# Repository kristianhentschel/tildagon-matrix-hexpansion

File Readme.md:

# Matrix Hexpansion

This repository contains the firmware and hardware projects for the **Matrix Hexpansion** and the CH32V006 breakout hexpansion it is based on. This is an add-on for the EMF Camp Tildagon/Spaceagon [badge](https://tildagon.badge.emfcamp.org/).

The hexpansion can be controlled with the [Matrix Hexpansion companion app](https://github.com/kristianhentschel/tildagon-matrix-hexpansion-app). The processor refreshes the LED Matrix using DMA (up to 156 LEDs with charlieplexing on its 13 available GPIO pins) and can run animated patterns or scrolling text configured by the badge over the I2C interface.

Assembled hexpansions will be available to buy from [shop.alwaysplottingsomething.com](https://shop.alwaysplottingsomething.com/category/hexpansions).

Note that the LEDs are only a single colour, and not as bright as the WS2812B/NeoPixel-style RGB LEDs seen on other hexpansions. On the other hand, you can have multiple of these plugged in without running down your battery in minutes!

## Base CH32V006 prototyping hexpansion

The common base board with the hexpansion connector must be produced with ENIG finish and holds the processor, status LEDs, configuration jumpers, and I2C pull-up resistors. It has large through hole pads for all GPIO pins and Hexpansion connector pins for a daughter board to connect to. There are also debug pads for I2C, power, and a USB programmer like the WCH LinkE.

I use the CH32V006F8U6/7 processor and program it with the [ch32fun framework](https://github.com/cnlohr/ch32fun). The CH32V003F4U6 has the same pinout and footprint, but may not have enough flash and RAM to run the matrix, control interface, and animation. If you get an assembled board from me, the processor is already programmed with a bootloader so firmware programs can be flashed from the badge without buying the dedicated USB debugger.

There is no dedicated EEPROM on the board, but the microcontroller is connected to the I2C bus and can emulate a read-only EEPROM interface if desired.

## Daughter board

Daughter boards are soldered to the base's pads, usually with SMD pads on the bottom. They can be cheaper to manufacture at low quantities (e.g. use HASL finish). The `lite-loop` board used in the Matrix Hexpansion is an example.

## Hardware

The `boards` directory contains KiCad projects and schematics for the PCBs.

* `base_v2_lite`: The base hexpansion board; with a CH32V006 co-processor and all GPIO pins and hexpansion interface pins broken out to through-hole pads.
* `lite_loop`: The 156-LED matrix display daughter board (13 pin charlie-plexing, arranged in 8 rows of 18 columns and a 9th row of 12 columns). Six instances of this make a circle surrounding the badge.

There is also a symbol library and footprints to aid in making custom daughter boards.

## Firmware

The RISC-V CH32V006 processor on the base board runs native firmware code built with the [ch32fun framework](https://github.com/cnlohr/ch32fun).

* `firmware/lite_loop` is the driver for the `lite-loop` daughter board. It maintains the LED matrix display, can run animations and scrolling text patterns, and presents an I2C interface for identifying and controlling the hexpansion from the badge.
* `firmware/bootloader_006` presents an I2C EEPROM-like interface if the `PD7` pin is pulled low during boot, so the badge can write the (non-bootloader) code flash area to replace the main program with a new firmware image.
* `firmware/blink` is a very small hello-world program that just toggles the PA1 pin attached to the status LED. It is useful when bulk provisioning or as a starting point for using the base without the lite-loop daughter board.

### Developing custom firmware

You can use the badge app to upload your own firmware program to the microcontroller on the hexpansion, for example to write your own animated patterns. To get set up you will need a few things:

1. A RISC-V toolchain, see instructions at https://github.com/cnlohr/ch32fun/wiki/Installation (building their `minichlink` and getting a USB debugger is optional as we will be using the badge to upload our firmware image).
2. A way to upload files to the badge over the USB connection, such as [mpremote](https://docs.micropython.org/en/latest/reference/mpremote.html) or [Thonny](https://thonny.org/).
3. The ["Matrix Hexpansion" app](https://apps.badge.emfcamp.org/apps/41214133), from the Tildagon app store.

Then follow these steps to upload firmware using the badge app:

1. Compile the firmware image
2. Copy the firmware image `.bin` file to the "Matrix Hexpansion" app's `assets/` folder
3. Reboop the badge
4. Open the app, and select "Firmware Upgrade", the target hexpansion slot, and your custom image.

```sh
# get the ch32fun repository
git submodule update --init --recursive

# make a copy of the lite-loop firmware to start from
cd firmware
cp -r lite_loop my_firmware

# build your firmware binary
cd my_firmware
make build

# copy the firmware image to the badge file system
mpremote cp main.bin :/apps/kristianhentschel_tildagon_matrix_hexpansion_app/assets/my_firmware.bin
```

To get started, place this code at the top of the `loop()` function in `my_firmware/main.c`:

```c
// void loop() {
  while(true) {
    for (int frame = 0; frame < 2 * LEDS_GRID_COLS; frame++) {
      for (int row = 0; row < LEDS_GRID_ROWS; row++) {
        for (int col = 0; col < LEDS_GRID_COLS; col++) {
          // Find the frame buffer index of the LED at the current row and column:
          int index = leds_grid_indices[row * LEDS_GRID_COLS + col];
          // In the array of grid indices some values are 255, because the first row only has 12 LEDs instead of 18, so skip those:
          if (index >= LEDS_COUNT) continue;
          
          // Set the LED to on or off depending on the current frame
          if (frame < LEDS_GRID_COLS) {
            frame_buffer[index] = col < frame ? 255 : 0;
          } else {
            frame_buffer[index] = col >= frame - LEDS_GRID_COLS ? 255 : 0;
          }
        }
      }

      Delay_Ms(40);
    }
  }

  // ... existing loop code, unreachable
// }
```

You may also wish to change the name in the hexpansion header; this will stop the app attempting to control it. Replace the `friendly_name` value in the hexpansion header (it must still be at most 9 characters; fill any extra slots with `0`):

```c
// static hexpansion_header_t g_hexpansion_header = {
  // ...
  // .friendly_name = {'L', 'i', 't', 'e', 'l', 'o', 'o', 'p', 0},
  .friendly_name = {'M', 'y', ' ', 'M', 'a', 't', 'r', 'i', 'x'},
// };
```

You can use the defined LED positions in [leds.h]() (using the `leds_polar_positions` and `leds_grid_indices` variables); or you could add to the list of animations, keep the name, and modify the badge app to trigger them.

Note this is all still somewhat of a prototype, for example I may change the position values to an integer representation, or come up with a system for the app to discover custom patterns to make this easier in future versions. It would also be nice to synchronise animations across multiple hexpansions.

### Bootloader and provisioning

To provision a factory-fresh processor, the bootloader must first be flashed and configured using a dedicated programmer like the WCH-LinkE and the ch32fun `minichlink` tool. We must flash the flash bootloader, configure PD7 use as GPIO rather than reset, and flash a main program. I use the `blink` program during provisioning because it is quick to build and upload; the lite_loop program is then flashed from the badge during testing. The `provision.sh` script does these steps, optionally in a loop:

```sh
./provision.sh --app blink --bootloader --loop
```
For end users, firmware updates can be applied from the badge app and a dedicated programmer is not required (but may still be helpful for debugging if writing your own firmware).

## Note on previous iteration

The base is called `v2` because the first iteration of this also had a [IS31FL3731](https://lumissil.com/assets/pdf/core/IS31FL3731_DS.pdf) LED driver, but this was found to add unnecessary cost and complexity and was never assembled or programmed properly. I suspect it would be able to drive the LED's quite a bit more brightly and consistently! In the current `v2` the current limiting resistors were moved to the daughter board and the breakout pads have a more useful generic layout, also including the hexpansion connector pins.

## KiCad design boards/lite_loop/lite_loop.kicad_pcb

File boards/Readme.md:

# Boards

* `base_v2_lite` is the base board. It has to be manufactured as a 1mm board with ENIG.
* `lite_loop` is the main "Matrix Hexpansion" LED daughter board. It can be connected to the top of the base board with solder paste and a hot air tool.

# Symbols and Footprints

* `matrix-hexpansion.kicad_sym` has schematic symbols for the base board's breakout pin array, including a version that only has the first two rows of pins as used on the `lite_loop` board.
* `matrix-hexpansion.pretty` is a footprint library including THT (used on the base) and SMD (used on the daughter boards) variations of the breakout pin array. The footprints have alignment aids on silkscreen and user layers.

# Acknowledgements

The base board is derived from the [badge-2024-hardware hexpansion template](https://github.com/emfcamp/badge-2024-hardware/tree/main/hexpansion) by kliment under CERN-OHL-P. The `hexpansion-edge-connector` symbol and footprint included with this repository for convenience are also from the same project.

# Stencils for previous version

If you want to make a stencil for your soldering kit picked up at EMF Camp 2026 (marked `v2`, `2026-05-22`), here are links to the [gerber files](https://stuff.5yk.de/20260719_lite_loop_gerber.zip) and [DXF exports](https://stuff.5yk.de/20260719_lite_loop_stencil.zip).

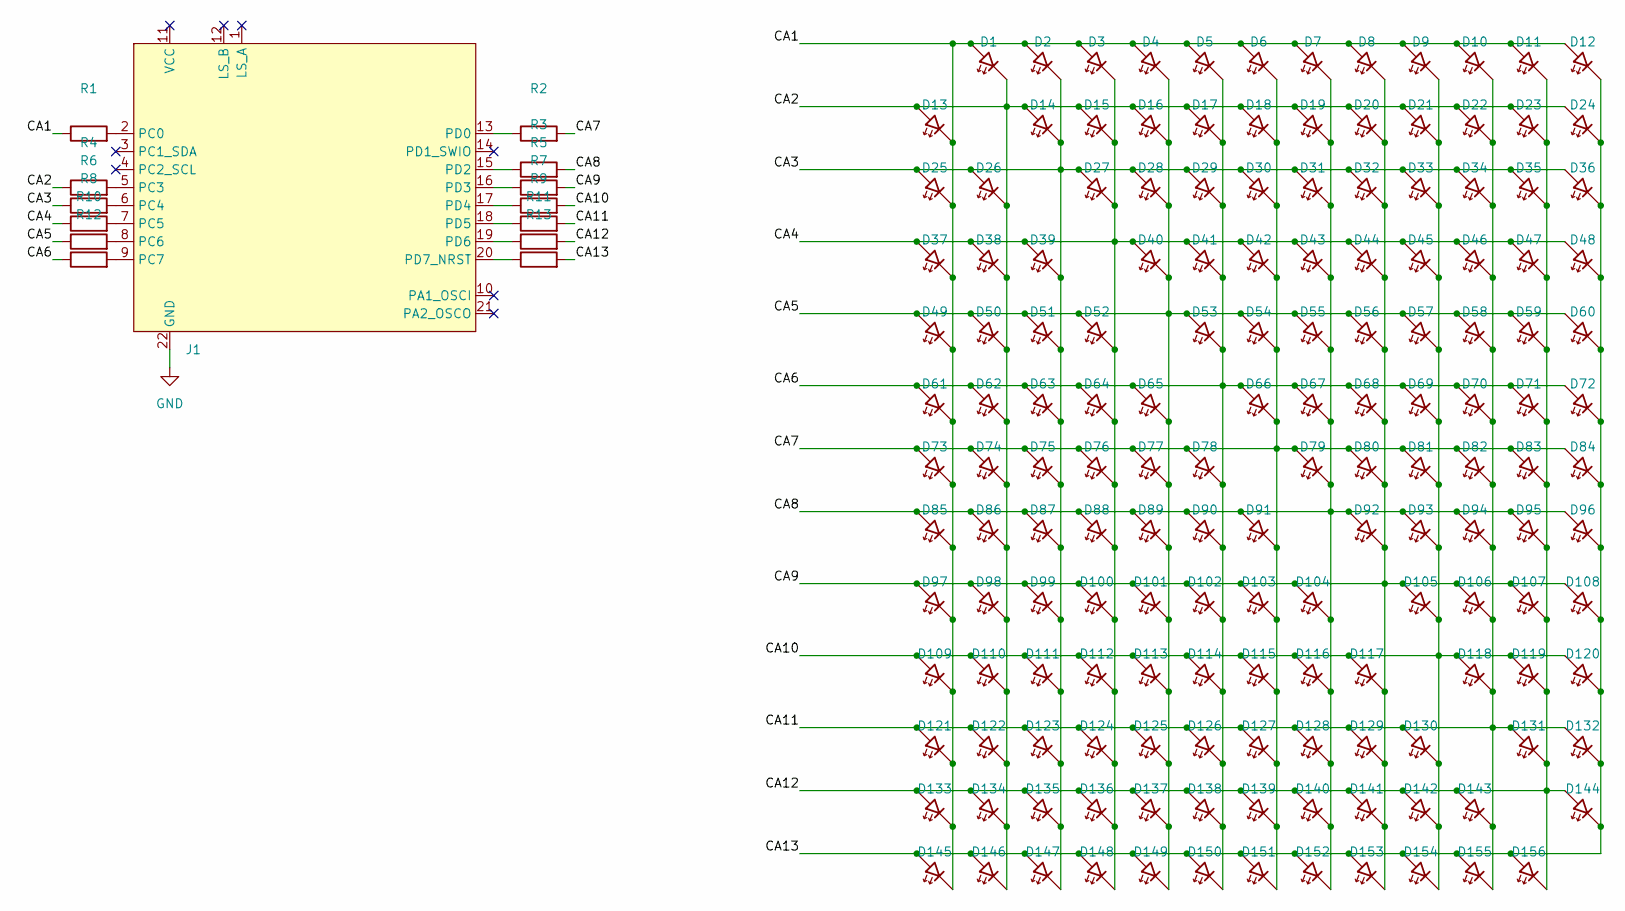
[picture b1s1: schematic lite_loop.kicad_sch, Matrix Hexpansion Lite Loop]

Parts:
D1, D2, D3, D4, D5, D6, D7, D8, D9, D10, D11, D12, D13, D14, D15, D16, D17, D18, D19, D20, D21, D22, D23, D24, D25, D26, D27, D28, D29, D30, D31, D32, D33, D34, D35, D36, D37, D38, D39, D40, D41, D42, D43, D44, D45, D46, D47, D48, D49, D50, D51, D52, D53, D54, D55, D56, D57, D58, D59, D60, D61, D62, D63, D64, D65, D66, D67, D68, D69, D70, D71, D72, D73, D74, D75, D76, D77, D78, D79, D80, D81, D82, D83, D84, D85, D86, D87, D88, D89, D90, D91, D92, D93, D94, D95, D96, D97, D98, D99, D100, D101, D102, D103, D104, D105, D106, D107, D108, D109, D110, D111, D112, D113, D114, D115, D116, D117, D118, D119, D120, D121, D122, D123, D124, D125, D126, D127, D128, D129, D130, D131, D132, D133, D134, D135, D136, D137, D138, D139, D140, D141, D142, D143, D144, D145, D146, D147, D148, D149, D150, D151, D152, D153, D154, D155, D156: LED; LED_0603_1608Metric
J1: matrix-hexpansion-base-v2-partial-SMD
R1, R2, R3, R4, R5, R6, R7, R8, R9, R10, R11, R12, R13: 100R; R_0603_1608Metric

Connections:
/CA1: D1.2 (A), D2.2 (A), D3.2 (A), D4.2 (A), D5.2 (A), D6.2 (A), D7.2 (A), D8.2 (A), D9.2 (A), D10.2 (A), D11.2 (A), D12.2 (A), D13.1 (K), D25.1 (K), D37.1 (K), D49.1 (K), D61.1 (K), D73.1 (K), D85.1 (K), D97.1 (K), D109.1 (K), D121.1 (K), D133.1 (K), D145.1 (K), R1.1
/CA2: D1.1 (K), D13.2 (A), D14.2 (A), D15.2 (A), D16.2 (A), D17.2 (A), D18.2 (A), D19.2 (A), D20.2 (A), D21.2 (A), D22.2 (A), D23.2 (A), D24.2 (A), D26.1 (K), D38.1 (K), D50.1 (K), D62.1 (K), D74.1 (K), D86.1 (K), D98.1 (K), D110.1 (K), D122.1 (K), D134.1 (K), D146.1 (K), R4.1
/CA3: D2.1 (K), D14.1 (K), D25.2 (A), D26.2 (A), D27.2 (A), D28.2 (A), D29.2 (A), D30.2 (A), D31.2 (A), D32.2 (A), D33.2 (A), D34.2 (A), D35.2 (A), D36.2 (A), D39.1 (K), D51.1 (K), D63.1 (K), D75.1 (K), D87.1 (K), D99.1 (K), D111.1 (K), D123.1 (K), D135.1 (K), D147.1 (K), R6.1
/CA4: D3.1 (K), D15.1 (K), D27.1 (K), D37.2 (A), D38.2 (A), D39.2 (A), D40.2 (A), D41.2 (A), D42.2 (A), D43.2 (A), D44.2 (A), D45.2 (A), D46.2 (A), D47.2 (A), D48.2 (A), D52.1 (K), D64.1 (K), D76.1 (K), D88.1 (K), D100.1 (K), D112.1 (K), D124.1 (K), D136.1 (K), D148.1 (K), R8.1
/CA5: D4.1 (K), D16.1 (K), D28.1 (K), D40.1 (K), D49.2 (A), D50.2 (A), D51.2 (A), D52.2 (A), D53.2 (A), D54.2 (A), D55.2 (A), D56.2 (A), D57.2 (A), D58.2 (A), D59.2 (A), D60.2 (A), D65.1 (K), D77.1 (K), D89.1 (K), D101.1 (K), D113.1 (K), D125.1 (K), D137.1 (K), D149.1 (K), R10.1
/CA6: D5.1 (K), D17.1 (K), D29.1 (K), D41.1 (K), D53.1 (K), D61.2 (A), D62.2 (A), D63.2 (A), D64.2 (A), D65.2 (A), D66.2 (A), D67.2 (A), D68.2 (A), D69.2 (A), D70.2 (A), D71.2 (A), D72.2 (A), D78.1 (K), D90.1 (K), D102.1 (K), D114.1 (K), D126.1 (K), D138.1 (K), D150.1 (K), R12.1
/CA7: D6.1 (K), D18.1 (K), D30.1 (K), D42.1 (K), D54.1 (K), D66.1 (K), D73.2 (A), D74.2 (A), D75.2 (A), D76.2 (A), D77.2 (A), D78.2 (A), D79.2 (A), D80.2 (A), D81.2 (A), D82.2 (A), D83.2 (A), D84.2 (A), D91.1 (K), D103.1 (K), D115.1 (K), D127.1 (K), D139.1 (K), D151.1 (K), R2.2
/CA8: D7.1 (K), D19.1 (K), D31.1 (K), D43.1 (K), D55.1 (K), D67.1 (K), D79.1 (K), D85.2 (A), D86.2 (A), D87.2 (A), D88.2 (A), D89.2 (A), D90.2 (A), D91.2 (A), D92.2 (A), D93.2 (A), D94.2 (A), D95.2 (A), D96.2 (A), D104.1 (K), D116.1 (K), D128.1 (K), D140.1 (K), D152.1 (K), R3.2
/CA9: D8.1 (K), D20.1 (K), D32.1 (K), D44.1 (K), D56.1 (K), D68.1 (K), D80.1 (K), D92.1 (K), D97.2 (A), D98.2 (A), D99.2 (A), D100.2 (A), D101.2 (A), D102.2 (A), D103.2 (A), D104.2 (A), D105.2 (A), D106.2 (A), D107.2 (A), D108.2 (A), D117.1 (K), D129.1 (K), D141.1 (K), D153.1 (K), R5.2
/CA10: D9.1 (K), D21.1 (K), D33.1 (K), D45.1 (K), D57.1 (K), D69.1 (K), D81.1 (K), D93.1 (K), D105.1 (K), D109.2 (A), D110.2 (A), D111.2 (A), D112.2 (A), D113.2 (A), D114.2 (A), D115.2 (A), D116.2 (A), D117.2 (A), D118.2 (A), D119.2 (A), D120.2 (A), D130.1 (K), D142.1 (K), D154.1 (K), R7.2
/CA11: D10.1 (K), D22.1 (K), D34.1 (K), D46.1 (K), D58.1 (K), D70.1 (K), D82.1 (K), D94.1 (K), D106.1 (K), D118.1 (K), D121.2 (A), D122.2 (A), D123.2 (A), D124.2 (A), D125.2 (A), D126.2 (A), D127.2 (A), D128.2 (A), D129.2 (A), D130.2 (A), D131.2 (A), D132.2 (A), D143.1 (K), D155.1 (K), R9.2
/CA12: D11.1 (K), D23.1 (K), D35.1 (K), D47.1 (K), D59.1 (K), D71.1 (K), D83.1 (K), D95.1 (K), D107.1 (K), D119.1 (K), D131.1 (K), D133.2 (A), D134.2 (A), D135.2 (A), D136.2 (A), D137.2 (A), D138.2 (A), D139.2 (A), D140.2 (A), D141.2 (A), D142.2 (A), D143.2 (A), D144.2 (A), D156.1 (K), R11.2
/CA13: D12.1 (K), D24.1 (K), D36.1 (K), D48.1 (K), D60.1 (K), D72.1 (K), D84.1 (K), D96.1 (K), D108.1 (K), D120.1 (K), D132.1 (K), D144.1 (K), D145.2 (A), D146.2 (A), D147.2 (A), D148.2 (A), D149.2 (A), D150.2 (A), D151.2 (A), D152.2 (A), D153.2 (A), D154.2 (A), D155.2 (A), D156.2 (A), R13.2
GND: J1.22 (GND)
unnamed: J1.2 (PC0), R1.2
unnamed: J1.5 (PC3), R4.2
unnamed: J1.6 (PC4), R6.2
unnamed: J1.7 (PC5), R8.2
unnamed: J1.8 (PC6), R10.2
unnamed: J1.9 (PC7), R12.2
unnamed: J1.13 (PD0), R2.1
unnamed: J1.15 (PD2), R3.1
unnamed: J1.16 (PD3), R5.1
unnamed: J1.17 (PD4), R7.1
unnamed: J1.18 (PD5), R9.1
unnamed: J1.19 (PD6), R11.1
unnamed: J1.20 (PD7_NRST), R13.1

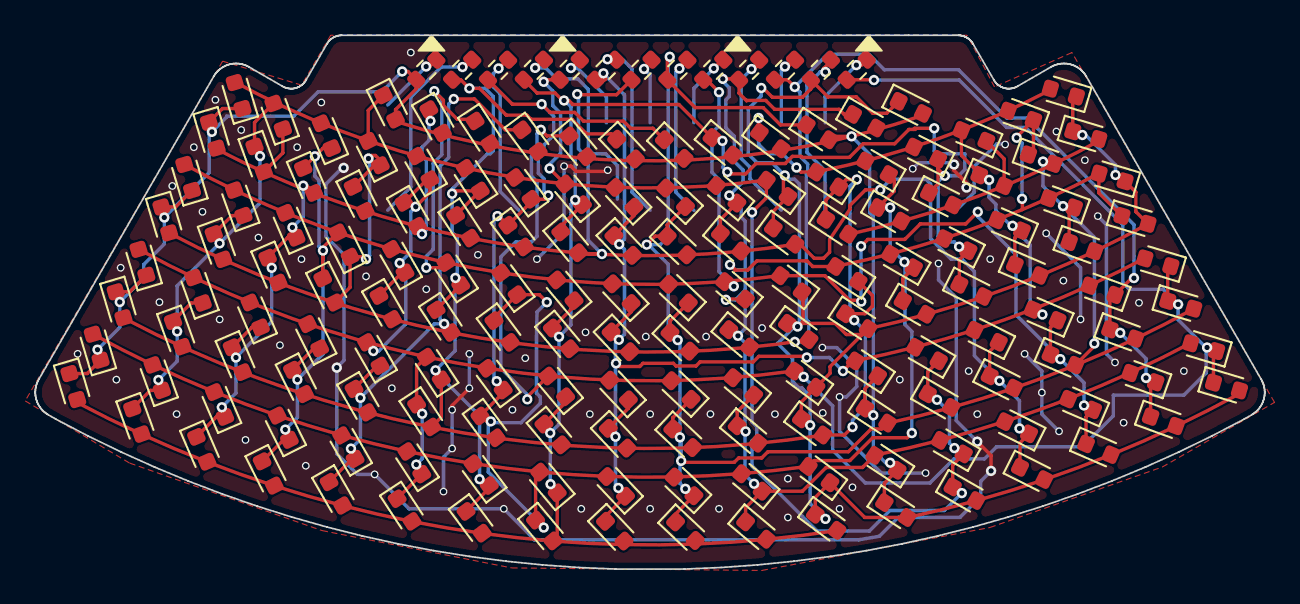
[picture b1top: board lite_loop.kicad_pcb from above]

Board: 2 copper layers, 71.4 x 31.0 mm, 170 parts (0 on the bottom side), 26 nets.

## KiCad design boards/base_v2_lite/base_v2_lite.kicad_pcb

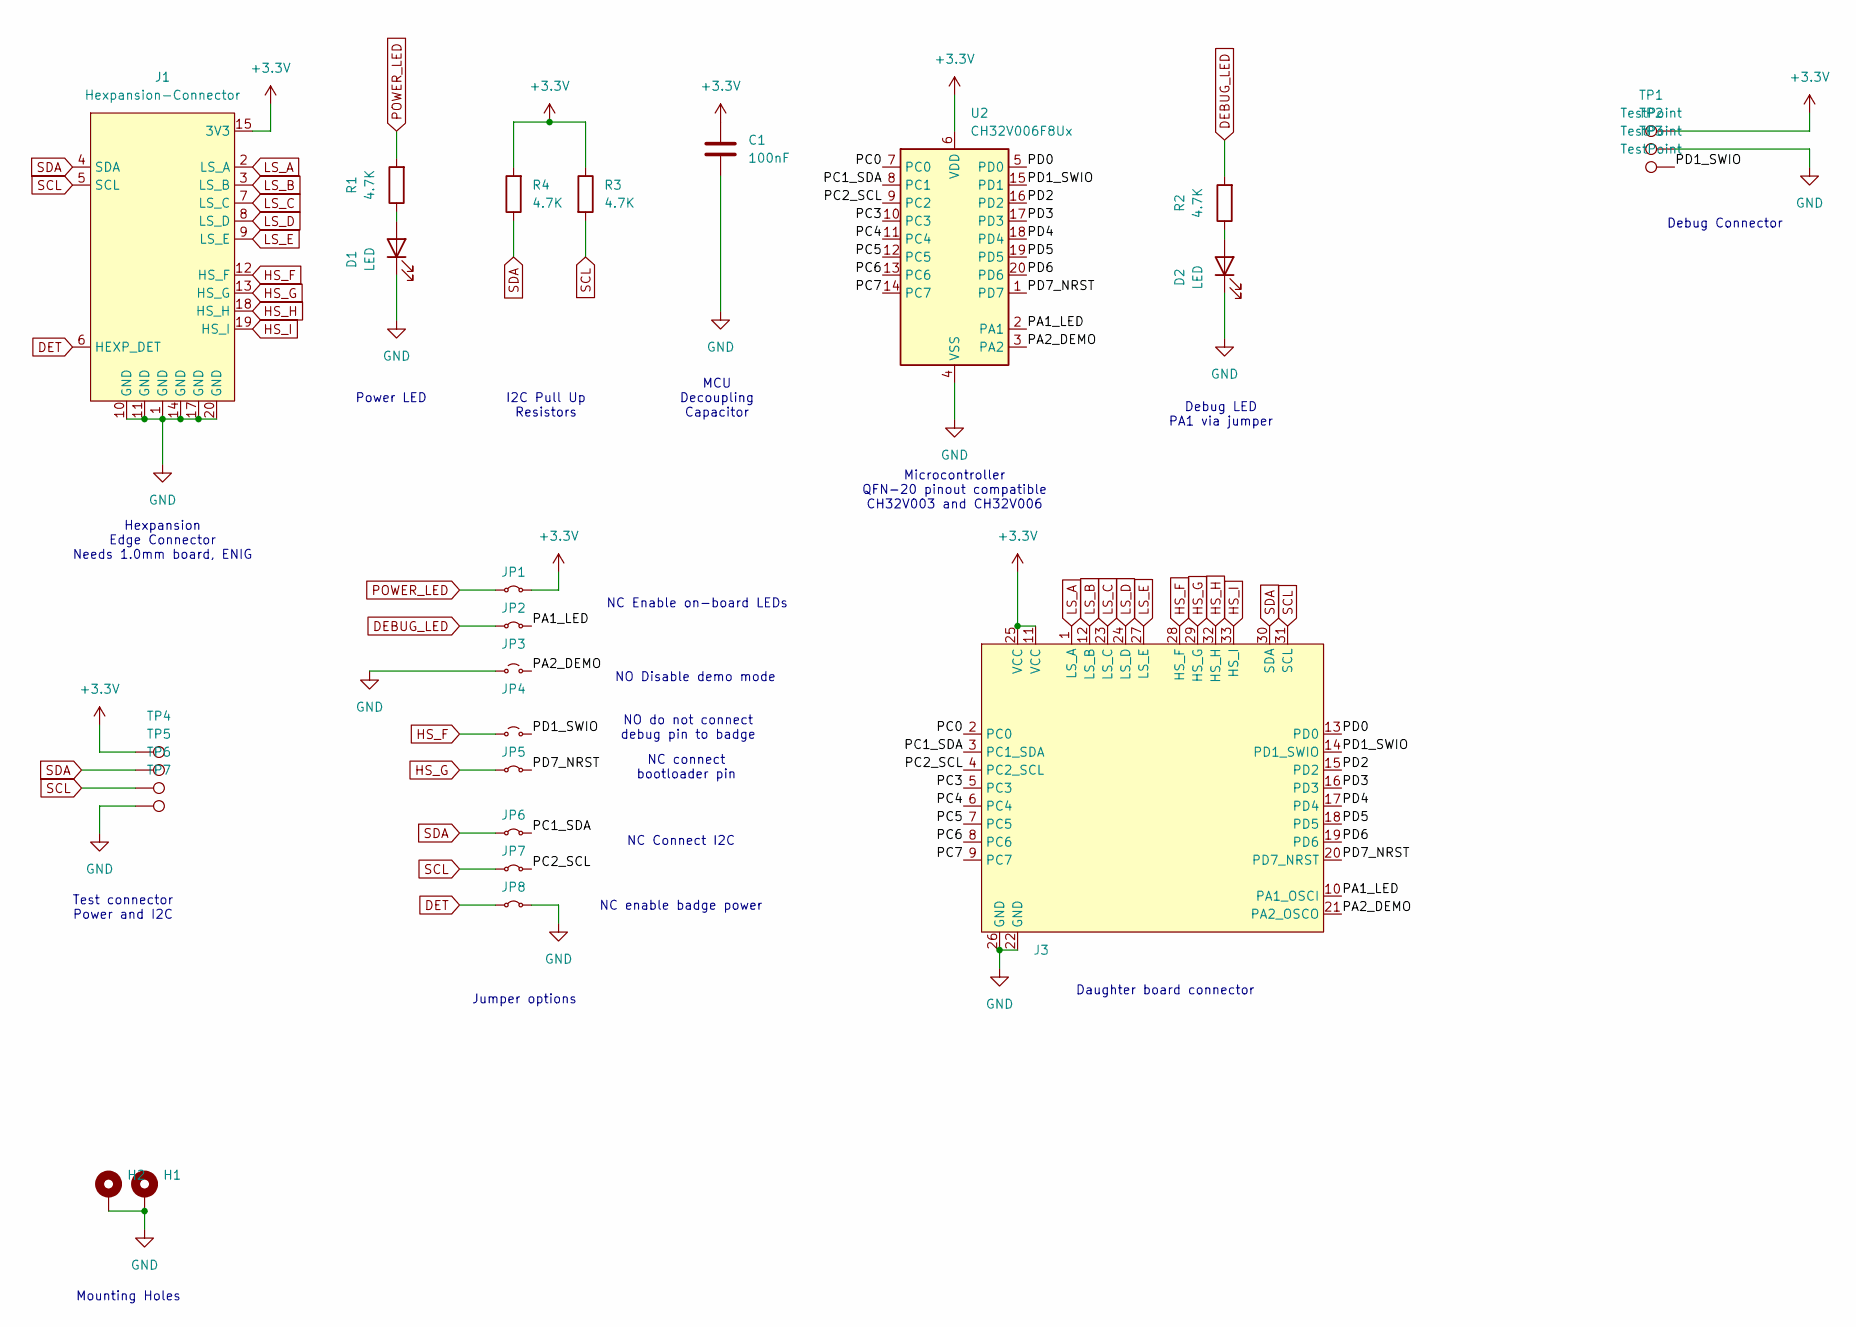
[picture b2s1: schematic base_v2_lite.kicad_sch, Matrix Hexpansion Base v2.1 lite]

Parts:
C1: 100nF; C_0603_1608Metric
D1, D2: LED; LED_0603_1608Metric
H1, H2: MountingHole_Pad; MountingHole_2.2mm_M2_Pad_Via
J1: Hexpansion-Connector; hexpansion-edge-connector
J3: matrix-hexpansion-base-v2-THT
JP1, JP2, JP5, JP6, JP7, JP8: Jumper_2_Small_Bridged; SolderJumper-2_P1.3mm_Bridged_Pad1.0x1.5mm
JP3, JP4: Jumper_2_Small_Open; SolderJumper-2_P1.3mm_Open_RoundedPad1.0x1.5mm
R1, R2, R3, R4: 4.7K; R_0603_1608Metric
TP1, TP3, TP4, TP5, TP6: TestPoint; TestPoint_THTPad_D1.5mm_Drill0.7mm
TP2, TP7: TestPoint; TestPoint_THTPad_1.5x1.5mm_Drill0.7mm
U2: CH32V006F8Ux; QFN-20-1EP_3x3mm_P0.4mm_EP1.65x1.65mm

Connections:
+3.3V: C1.1, J1.15 (3V3), J1.16 (3V3), J3.11 (VCC), J3.25 (VCC), JP1.2 (B), R3.1, R4.2, TP1.1 (1_1), TP4.1 (1_1), U2.6 (VDD)
/PA1_LED: J3.10 (PA1_OSCI), JP2.2 (B), U2.2 (PA1)
/PA2_DEMO: J3.21 (PA2_OSCO), JP3.2 (B), U2.3 (PA2)
/PC0: J3.2 (PC0), U2.7 (PC0)
/PC1_SDA: J3.3 (PC1_SDA), JP6.2 (B), U2.8 (PC1)
/PC2_SCL: J3.4 (PC2_SCL), JP7.2 (B), U2.9 (PC2)
/PC3: J3.5 (PC3), U2.10 (PC3)
/PC4: J3.6 (PC4), U2.11 (PC4)
/PC5: J3.7 (PC5), U2.12 (PC5)
/PC6: J3.8 (PC6), U2.13 (PC6)
/PC7: J3.9 (PC7), U2.14 (PC7)
/PD0: J3.13 (PD0), U2.5 (PD0)
/PD1_SWIO: J3.14 (PD1_SWIO), JP4.2 (B), TP3.1 (1_1), U2.15 (PD1)
/PD2: J3.15 (PD2), U2.16 (PD2)
/PD3: J3.16 (PD3), U2.17 (PD3)
/PD4: J3.17 (PD4), U2.18 (PD4)
/PD5: J3.18 (PD5), U2.19 (PD5)
/PD6: J3.19 (PD6), U2.20 (PD6)
/PD7_NRST: J3.20 (PD7_NRST), JP5.2 (B), U2.1 (PD7)
DEBUG_LED: JP2.1 (A), R2.2
DET: J1.6 (HEXP_DET), JP8.1 (A)
GND: C1.2, D1.1 (K), D2.1 (K), H1.1 (1_1), H2.1 (1_1), J1.1 (GND), J1.10 (GND), J1.11 (GND), J1.14 (GND), J1.17 (GND), J1.20 (GND), J3.22 (GND), J3.26 (GND), JP3.1 (A), JP8.2 (B), TP2.1 (1_1), TP7.1 (1_1), U2.4 (VSS), U2.21 (VSS)
HS_F: J1.12 (HS_F), J3.28 (HS_F), JP4.1 (A)
HS_G: J1.13 (HS_G), J3.29 (HS_G), JP5.1 (A)
HS_H: J1.18 (HS_H), J3.32 (HS_H)
HS_I: J1.19 (HS_I), J3.33 (HS_I)
LS_A: J1.2 (LS_A), J3.1 (LS_A)
LS_B: J1.3 (LS_B), J3.12 (LS_B)
LS_C: J1.7 (LS_C), J3.23 (LS_C)
LS_D: J1.8 (LS_D), J3.24 (LS_D)
LS_E: J1.9 (LS_E), J3.27 (LS_E)
unnamed: D1.2 (A), R1.1
unnamed: D2.2 (A), R2.1
POWER_LED: JP1.1 (A), R1.2
SCL: J1.5 (SCL), J3.31 (SCL), JP7.1 (A), R3.2, TP6.1 (1_1)
SDA: J1.4 (SDA), J3.30 (SDA), JP6.1 (A), R4.1, TP5.1 (1_1)

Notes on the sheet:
Hexpansion Edge Connector Needs 1.0mm board, ENIG
Mounting Holes
NO Disable demo mode
NC Enable on-board LEDs
MCU Decoupling Capacitor
Test connector Power and I2C
NC connect bootloader pin
Microcontroller QFN-20 pinout compatible CH32V003 and CH32V006
Debug LED PA1 via jumper
NC enable badge power
I2C Pull Up Resistors
Jumper options
Power LED
Daughter board connector
Debug Connector
NO do not connect debug pin to badge
NC Connect I2C

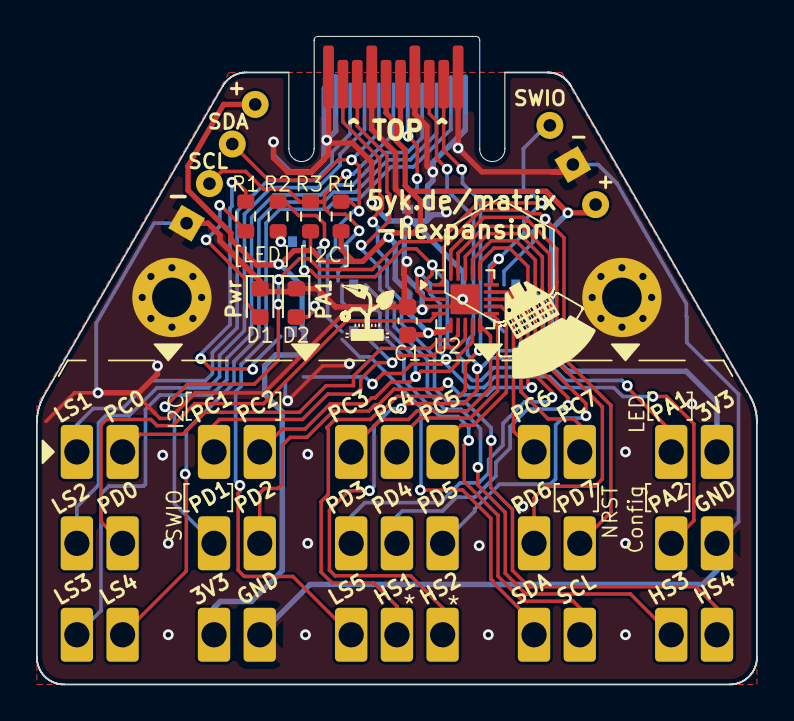
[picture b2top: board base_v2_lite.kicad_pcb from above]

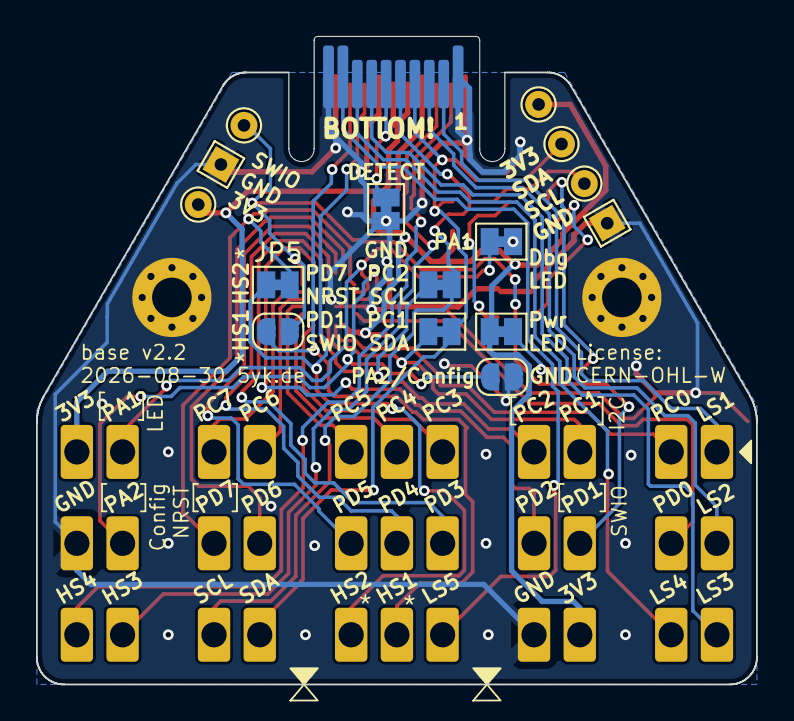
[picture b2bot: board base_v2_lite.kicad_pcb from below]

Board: 2 copper layers, 40.0 x 36.0 mm, 27 parts (15 on the bottom side), 36 nets.

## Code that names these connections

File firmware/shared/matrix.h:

#ifndef MATRIX_H
#define MATRIX_H
// === Framework and standard includes ===
#include "ch32fun.h"
#include <stdint.h>
#include <stdio.h>

// === Options ===

// The PWM count and number type that can hold numbers up to MATRIX_PWM_COUNT - 1.
// Must be a power of two between 256 and 4096, and either uint8_t or uint16_t.

// Currently working values:
// - bits = 7, prescaler = 0x10, ~50fps (preferred)
// - bits = 8, prescaler = 0x11, ~25fps

#define MATRIX_PWM_BITS 7
#define MATRIX_PWM_COUNT 1 << MATRIX_PWM_BITS
#define MATRIX_BUF_SIZE MATRIX_PWM_COUNT // TODO allow reducing this to save on SRAM
#define MATRIX_TIM1_PRESCALER 0x0010 // TODO attempt to reduce to increase column scan rate and reduce flicker

typedef uint8_t matrix_pwm_t;

// Choose the layout by uncommenting _one_ of these options:
// #define BOTTLESHIP_CONFIG_6x15 // 6x15 matrix for 90 LEDs using 10 pins
#define BOTTLESHIP_CONFIG_HEX_61 // two matrices of 6x5 = 60 pins (TODO plus one special one not considered)
// #define BOTTLESHIP_CONFIG_72R5 // 5 rings for 72 LEDs using 9 pins

// === Layout-specific options ===

// Number of LEDs in this layout
// Combining the ports and addressing them as one matrix with 13 pins allows addressing up to 156 LEDs.
#ifndef MATRIX_NUM_LEDS
#define MATRIX_NUM_LEDS 156
#endif

// Independent mode provides brighter LEDs and faster refresh cycles but can only address up to 72.
// #define MATRIX_INDEPENDENT_PORTS

// Number of Port C and Port D pins used
// Reduce this for smaller matrices
#ifndef MATRIX_NUM_GPIOC_PINS
#define MATRIX_NUM_GPIOC_PINS 6
#endif
#ifndef MATRIX_NUM_GPIOD_PINS
#define MATRIX_NUM_GPIOD_PINS 7
#endif

// Pin numbers
// On port C we can use 6 pins, skipping the I2C pins PC1 and PC2
#define MATRIX_GPIOC_0 0
#define MATRIX_GPIOC_1 3
#define MATRIX_GPIOC_2 4
#define MATRIX_GPIOC_3 5
#define MATRIX_GPIOC_4 6
#define MATRIX_GPIOC_5 7

// On port D, we can use 7 pins (including PD7), just skipping PD1 as that is used for SWIO
// Note: if PD7 is used, the NRST function must be disabled once in user option bytes with `minichlink -D`
#define MATRIX_GPIOD_0 0
#define MATRIX_GPIOD_1 2
#define MATRIX_GPIOD_2 3
#define MATRIX_GPIOD_3 4
#define MATRIX_GPIOD_4 5
#define MATRIX_GPIOD_5 6
#define MATRIX_GPIOD_6 7

// Extra LED on PD0, last in "wiring order"
// #define MATRIX_EXTRA_LED_GPIOD 0

// === Calculated declarations ===
// The below lines should not need to be changed for a new layout

// Calculate total number of pins and positions
#define MATRIX_NUM_PINS  (MATRIX_NUM_GPIOC_PINS + MATRIX_NUM_GPIOD_PINS)

// We assume charlieplex wiring using pins from GPIO ports C and D in the order defined in these arrays (first C, then D)
extern volatile const uint8_t MATRIX_GPIOC_PINS[MATRIX_NUM_GPIOC_PINS];
extern volatile const uint8_t MATRIX_GPIOD_PINS[MATRIX_NUM_GPIOD_PINS];


// === Methods ===

// Initialises the DMA, Timer1, and GPIO peripherals to drive the charlieplexed matrix on the pins
// defined in MATRIX_GPIOC/D_PINS.
// The frame buffer must have the configured MATRIX_NUM_LEDS entries.
// Takes control of the OUTDR for both GPIO ports but only reconfigures CFGR for the matrix pins.
// Unused pins may still be read or driven by other peripherals, they just cannot be used as GPIO outputs.
void matrix_setup(volatile matrix_pwm_t *frame_buffer);

// Replaces the frame buffer the LED PWM values are read from instantly (ie mid-frame or mid-line).
// The frame buffer must have the configured MATRIX_NUM_LEDS entries.
void matrix_swap_buffer(volatile matrix_pwm_t *frame_buffer);

// === Error checking ===
#ifndef MATRIX_NUM_LEDS
#error "config must define MATRIX_NUM_LEDS"
#endif

#ifndef MATRIX_PWM_COUNT
#error "config must define MATRIX_PWM_COUNT"
#endif

#if MATRIX_PWM_COUNT > 256
#error "MATRIX_PWM_COUNT should be <= 256"
#endif

#ifdef MATRIX_INDEPENDENT_PORTS
  #if MATRIX_NUM_LEDS > (MATRIX_NUM_GPIOC_PINS * (MATRIX_NUM_GPIOC_PINS - 1) + MATRIX_NUM_GPIOD_PINS * (MATRIX_NUM_GPIOD_PINS - 1))
  #error "MATRIX_NUM_LEDS is too large for the number of pins in independent port mode"
  #endif
#else
  #if MATRIX_NUM_LEDS > (MATRIX_NUM_PINS * (MATRIX_NUM_PINS - 1))
  #error "MATRIX_NUM_LEDS is too large for the number of pins in combined mode"
  #endif
#endif

#endif // MATRIX_H

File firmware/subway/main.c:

#include "ch32fun.h"
#include <stdio.h>
#include "../shared/debug_printf.h"
#include "../shared/hexpansion_header.h"
#include "../shared/i2c_again.h"
#include "../shared/matrix.h"
#include "lib_rand.h"

#define BTN_LEFT_PIN PA2
#define BTN_RIGHT_PIN PA1

void loop() __attribute__((section(".srodata")));

matrix_pwm_t frame_buffer[MATRIX_NUM_LEDS];

static hexpansion_header_t g_hexpansion_header = {
  .magic = {'T', 'H', 'E', 'X'},
  .manifest_version = {'2', '0', '2', '4'},
  .filesystem_info = {
    .offset = 32, // offset from start of eeprom, must be multiple of page size
    .page_size = 32, // emulated eeprom page size (not littlefs block size I think)
    .total_size = 0, // emulated space, reads past fs will return zero
  },
  .vendor_id = 0xCAFE,
  .product_id = 0x54E1,
  .unique_id = 0x0000,
  .friendly_name = {'S', 'h', 'o', 'o', 'g', 'l', 'e', 0, 0},
};

static const i2c_config_t g_i2c_config = {
  .primary_address = 0x20,
  .primary_num_pages = 0, // primary I2C interface not used yet
  .primary_page_definitions = NULL,

  .secondary_address = 0x50, // EEPROM on 0x50 (expected fixed address by companion app)
  .secondary_header =  &g_hexpansion_header,
  .secondary_fs = NULL,
  .secondary_fs_size = 0,
};

int main()
{
  SystemInit();
  Delay_Ms(50);

  funGpioInitAll();

  // Configure button pins as inputs with pull up
  funPinMode(BTN_LEFT_PIN, GPIO_CNF_IN_PUPD);
  funPinMode(BTN_RIGHT_PIN, GPIO_CNF_IN_PUPD);
  funDigitalWrite(BTN_LEFT_PIN, FUN_HIGH);
  funDigitalWrite(BTN_RIGHT_PIN, FUN_HIGH);

  // Configure I2C pins (TODO why isn't this in i2c_setup)
  funPinMode(PC1, GPIO_CFGLR_OUT_10Mhz_AF_OD); // SDA
  funPinMode(PC2, GPIO_CFGLR_OUT_10Mhz_AF_OD); // SCL

  hexpansion_header_fill_checksum(&g_hexpansion_header);

  matrix_setup(frame_buffer);

  i2c_setup(&g_i2c_config);

  loop();
}

#define NUM_TRAINS 16
#define LEDS_PER_CIRCLE 30
#define RESOLUTION 30
#define NUM_POSITIONS (RESOLUTION*LEDS_PER_CIRCLE)
#define NUM_STATIONS 15
#define STATION_SPACING (RESOLUTION * LEDS_PER_CIRCLE / NUM_STATIONS)
#define STATION_OFFSET (RESOLUTION / 2)
#define FRAME_PERIOD 20
#define STOPPING_TIME 100
// TODO define a rand() wrapper to scale with resolution

// Gamma brightness lookup table <https://victornpb.github.io/gamma-table-generator>
// gamma = 2.70 steps = 256 range = 0-255
const uint8_t gamma_lut[256] = {
  0,   0,   0,   0,   0,   0,   0,   0,   0,   0,   0,   0,   0,   0,   0,   0,
  0,   0,   0,   0,   0,   0,   0,   0,   0,   0,   1,   1,   1,   1,   1,   1,
  1,   1,   1,   1,   1,   1,   1,   2,   2,   2,   2,   2,   2,   2,   3,   3,
  3,   3,   3,   3,   3,   4,   4,   4,   4,   4,   5,   5,   5,   5,   6,   6,
  6,   6,   7,   7,   7,   7,   8,   8,   8,   9,   9,   9,  10,  10,  10,  11,
  11,  12,  12,  12,  13,  13,  14,  14,  14,  15,  15,  16,  16,  17,  17,  18,
  18,  19,  19,  20,  20,  21,  21,  22,  23,  23,  24,  24,  25,  26,  26,  27,
  28,  28,  29,  30,  30,  31,  32,  33,  33,  34,  35,  36,  36,  37,  38,  39,
  40,  41,  41,  42,  43,  44,  45,  46,  47,  48,  49,  50,  51,  51,  52,  53,
  55,  56,  57,  58,  59,  60,  61,  62,  63,  64,  65,  66,  68,  69,  70,  71,
  72,  74,  75,  76,  77,  79,  80,  81,  83,  84,  85,  87,  88,  89,  91,  92,
  94,  95,  97,  98, 100, 101, 103, 104, 106, 107, 109, 110, 112, 114, 115, 117,
  119, 120, 122, 124, 125, 127, 129, 131, 132, 134, 136, 138, 140, 141, 143, 145,
  147, 149, 151, 153, 155, 157, 159, 161, 163, 165, 167, 169, 171, 173, 175, 178,
  180, 182, 184, 186, 188, 191, 193, 195, 198, 200, 202, 205, 207, 209, 212, 214,
  216, 219, 221, 224, 226, 229, 231, 234, 237, 239, 242, 244, 247, 250, 252, 255,
};

typedef struct train {
  uint16_t pos;
  uint8_t speed;
  uint8_t dwell;
  uint16_t next_station_pos;
  int8_t direction;
} train_t;

void loop() {
  // TODO random starting positions
  train_t trains[NUM_TRAINS];
  uint8_t scratch[NUM_POSITIONS];

  for (int i = 0; i < NUM_TRAINS; i++) {
    uint16_t pos = (STATION_OFFSET + i * STATION_SPACING) % NUM_POSITIONS;
    train_t train = {
      .pos = pos,
      .speed = 1,
      .dwell = (rand() & 0xff),
      .next_station_pos = pos,
      .direction = i % 2 ? -1 : 1,
    };

    trains[i] = train;
  }

  while(1)
  {
    uint32_t frame_start = SysTick->CNT;

    // TODO more interesting movement logic (eg. stop at stations, no overtaking, acceleration and braking)
    // Advance all train positions
    for (int i = 0; i < NUM_TRAINS; i++) {
      train_t *train = &trains[i];

      // pause if reached the next station
      if (train->pos == train->next_station_pos) {
        train->dwell = STOPPING_TIME + (rand() & 0x3F);
        train->next_station_pos = (NUM_POSITIONS + train->pos + train->direction * STATION_SPACING) % NUM_POSITIONS;

        train->speed = (rand() & 0xF) > 10 ? 2 : 1; // Some trains are just faster, sometimes. NB speed must evenly divide into station spacing
      }

      // pause if there is a train in front
      if (train->dwell == 0) {
        for (int j = 0; j < NUM_TRAINS; j++) {
          train_t *other = &trains[j];
          if (i != j && train->direction == other->direction) {
            if ((NUM_POSITIONS + train->direction * other->pos - train->direction * train->pos) % NUM_POSITIONS <= STATION_SPACING / 2) {
              train->dwell = (rand() & 0xF);
              break;
            }
          }
        }
      }

      // decrement dwell time or move at max speed
      if (train->dwell > 0) {
        train->dwell--;
      } else {
        train->pos = (NUM_POSITIONS + train->pos + train->speed * train->direction) % NUM_POSITIONS;
      }
    }

    // Update LEDs
    for (int i = 0; i < 2; i++) {
      uint8_t offset = i * LEDS_PER_CIRCLE;

      // clear
      for (int j = 0; j < NUM_POSITIONS; j++) {
        scratch[j] = 0;
      }

      // fill in high resolution positions occupied by the train
      for (int j = 0; j < NUM_TRAINS; j++) {
        // skip trains on the other circle
        if (trains[j].direction != (i == 0 ? 1 : -1)) {
          continue;
        }

        uint16_t pos = trains[j].pos;
        for (int k = 0; k < RESOLUTION; k++) {
          scratch[(pos + k) % NUM_POSITIONS] = 1;
        }
      }

      // reduce by counting the number of occupied high resolution positions mapped to each LED
      for (int j = 0; j < LEDS_PER_CIRCLE; j++) {
        uint8_t sum = 0;
        for (int k = 0; k < RESOLUTION; k++) {
          sum = sum + scratch[(NUM_POSITIONS + j * RESOLUTION - RESOLUTION / 2 + k) % NUM_POSITIONS];
        }
        frame_buffer[j + offset] = gamma_lut[sum * (255 / RESOLUTION)];
        if (frame_buffer[j + offset] == 0) {
          frame_buffer[j + offset] = 1;
        }
      }
    }

    while (TimeElapsed32u(SysTick->CNT, frame_start) < Ticks_from_Ms(FRAME_PERIOD)) {
      ;
    }
  }
}

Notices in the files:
boards/base_v2_lite/base_v2_lite.kicad_pcb:
CERN-OHL-W
License: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
